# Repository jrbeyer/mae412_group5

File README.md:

# Custom Model Train System With Pan-Tilt Tracking, Positioning, and Aiming Sentries

This repository contains the codebase for a custom model train system control. The system uses two pan-tilt turrets, one for searching and tracking a train as it follows a track, and the other for hitting the train with a laser from any region of the track.

## System Overview

The system is designed around two custom 3D printed pan-tilt turrets, each equipped with a NEMA 17 stepper motor, variable current motor drivers, and AS5600 motor encoders. The turrets use specific ratio gear pulleys for precise control.

The train system is controlled by a Hornbee train controller system and a custom microprocessor implemented on a scotchflex vector board consisting of an EEPROM, ACIA, and other components. The system interfaces with two ESP32-S2-Minis and custom power sensor fusion and motor control boards.

## Features

- **Train Tracking**: Uses a PixyCam and a Time-of-Flight (ToF) sensor to search and track the train. The system outputs the global coordinates of the train via ESP32.
- **Laser Control**: Takes in the reported coordinates of the train and controls a laser to hit the train from any region of the track.

## Hardware Requirements

- ESP32-S2-Minis
- PixyCam
- Time-of-Flight (ToF) sensor
- Pan-Tilt Turrets (Custom 3D printed)
- NEMA 17 Stepper Motors
- Variable Current Motor Drivers
- AS5600 Motor Encoders
- Specific Ratio Gear Pulleys
- Laser Pointer
- Hornbee Train Controller System
- Custom Microprocessor (Implemented on a Scotchflex Vector Board)
- Custom Power Sensor Fusion and Motor Control Boards

## Software Requirements

- Arduino IDE
- VL53L0X Library
- Pixy Library
- BasicStepperDriver Library

## Setup

1. Connect the PixyCam and ToF sensor to the ESP32.
2. Connect the pan-tilt turrets to the ESP32.
3. Connect the laser pointer to the ESP32.
4. Open the `mae412_group5.ino` file in the Arduino IDE.
5. Upload the code to the ESP32.

## Usage

The system operates in three states:

- **Inactive**: The system is idle and the steppers are disabled.
- **Search**: The system searches for the train using the PixyCam and ToF sensor. The steppers are enabled and move the turret to track the train.
- **Lock**: The system locks onto the train and the laser pointer is activated. The turret moves to follow the train and the laser pointer adjusts to hit the train.

## Contributing

Pull requests are welcome. For major changes, please open an issue first to discuss what you would like to change.

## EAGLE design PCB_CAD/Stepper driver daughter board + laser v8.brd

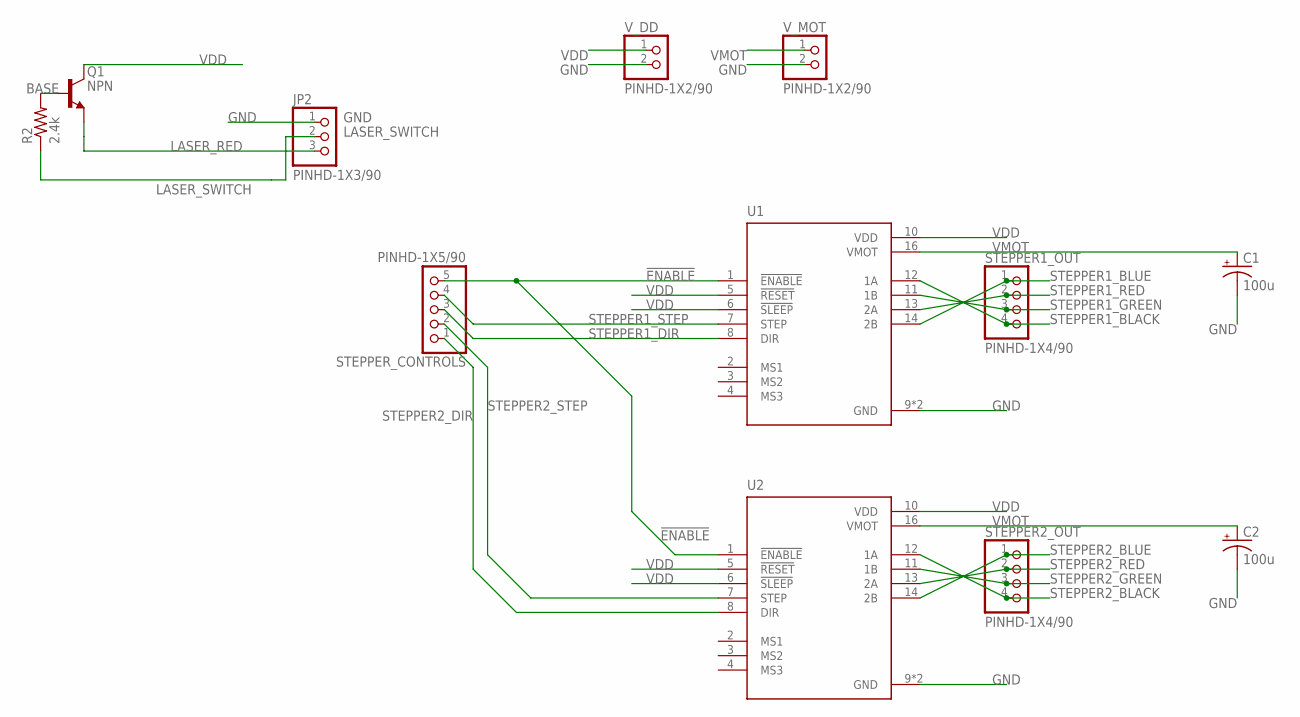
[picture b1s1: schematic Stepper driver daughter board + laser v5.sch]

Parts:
C1, C2: 100u; E22-6
JP2: PINHD-1X3/90; 1X03/90
Q1: NPN; TO92
R2: 2.4k; 0207/10
STEPPER1_OUT, STEPPER2_OUT: PINHD-1X4/90; 1X04/90
STEPPER_CONTROLS: PINHD-1X5/90; 1X05/90
U1, U2: A4988_STEPPER_MOTOR_DRIVER_CARRIER; MODULE_A4988_STEPPER_MOTOR_DRIVER_CARRIER
V_DD: PINHD-1X2/90; 1X02/90
V_MOT: PINHD-1X2/90; 1X02/90

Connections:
!ENABLE: STEPPER_CONTROLS.5, U1.1 (!ENABLE), U2.1 (!ENABLE)
BASE: Q1.2 (B), R2.2
GND: C1.-, C2.-, JP2.1, U1.9 (GND), U1.15 (GND), U2.9 (GND), U2.15 (GND), V_DD.2, V_MOT.2
LASER_RED: JP2.3, Q1.1 (E)
LASER_SWITCH: JP2.2, R2.1
STEPPER1_BLACK: STEPPER1_OUT.4, U1.12 (1A)
STEPPER1_BLUE: STEPPER1_OUT.1, U1.14 (2B)
STEPPER1_DIR: STEPPER_CONTROLS.3, U1.8 (DIR)
STEPPER1_GREEN: STEPPER1_OUT.3, U1.11 (1B)
STEPPER1_RED: STEPPER1_OUT.2, U1.13 (2A)
STEPPER1_STEP: STEPPER_CONTROLS.4, U1.7 (STEP)
STEPPER2_BLACK: STEPPER2_OUT.4, U2.12 (1A)
STEPPER2_BLUE: STEPPER2_OUT.1, U2.14 (2B)
STEPPER2_DIR: STEPPER_CONTROLS.1, U2.8 (DIR)
STEPPER2_GREEN: STEPPER2_OUT.3, U2.11 (1B)
STEPPER2_RED: STEPPER2_OUT.2, U2.13 (2A)
STEPPER2_STEP: STEPPER_CONTROLS.2, U2.7 (STEP)
VDD: Q1.3 (C), U1.5 (!RESET), U1.6 (!SLEEP), U1.10 (VDD), U2.5 (!RESET), U2.6 (!SLEEP), U2.10 (VDD), V_DD.1
VMOT: C1.+, C2.+, U1.16 (VMOT), U2.16 (VMOT), V_MOT.1

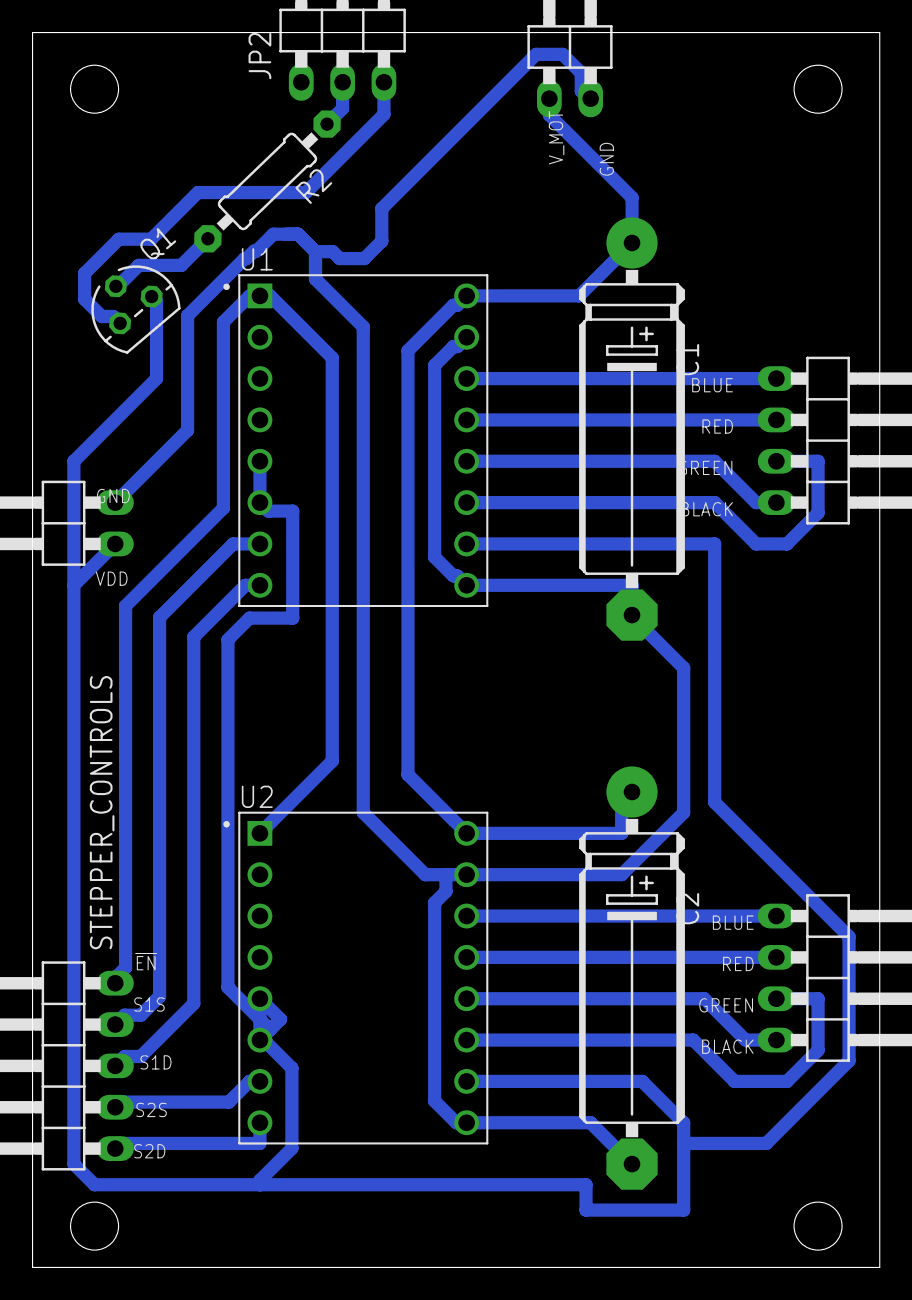
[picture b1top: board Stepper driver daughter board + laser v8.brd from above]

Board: 2 copper layers, 52.0 x 75.9 mm, 12 parts (0 on the bottom side), 19 nets.

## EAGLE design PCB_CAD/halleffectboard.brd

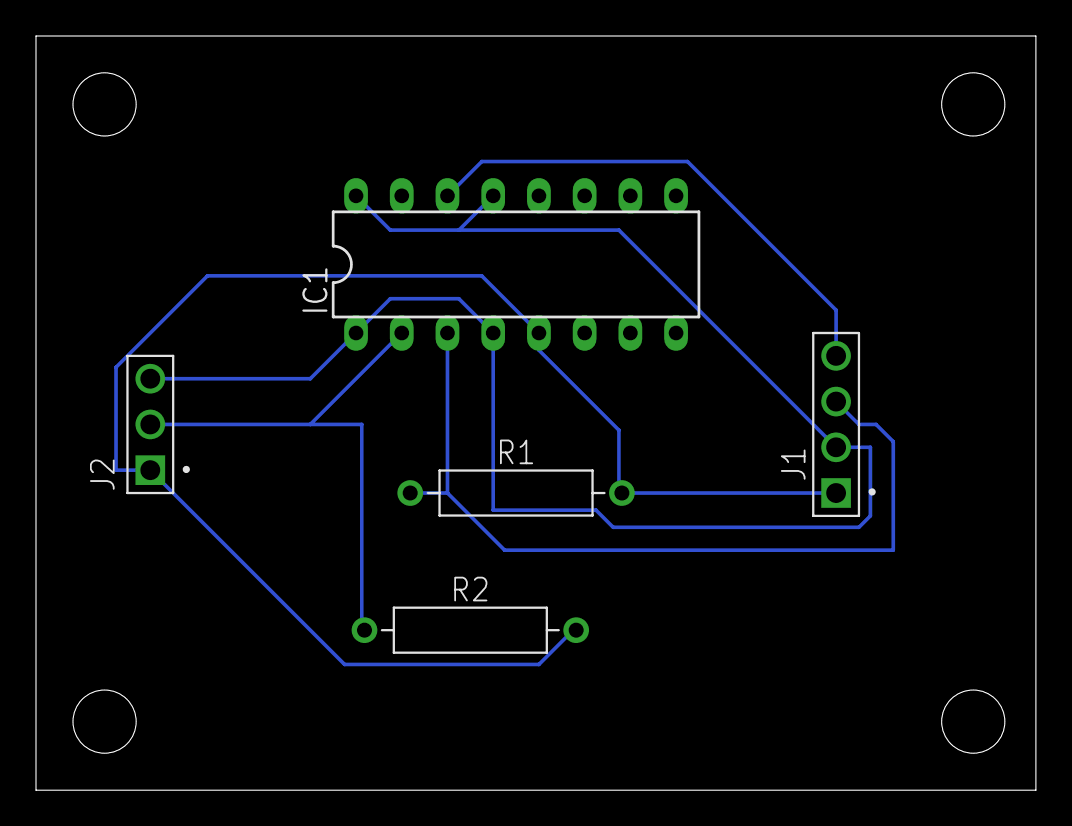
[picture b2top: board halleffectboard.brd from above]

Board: 2 copper layers, 55.5 x 41.9 mm, 5 parts (0 on the bottom side), 5 nets.

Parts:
IC1: 7476N; DIL16
J1: 61300411121
J2: 61300311121
R1, R2: RESAD1176W63L850D250B

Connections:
CLR: IC1.3, J1.3, R1.1
GND: IC1.1, IC1.4, IC1.13, IC1.16, J1.2, J2.3
HALL: IC1.2, J2.2, R2.1
OUT: IC1.14, J1.4
VCC: IC1.5, J1.1, J2.1, R1.2, R2.2

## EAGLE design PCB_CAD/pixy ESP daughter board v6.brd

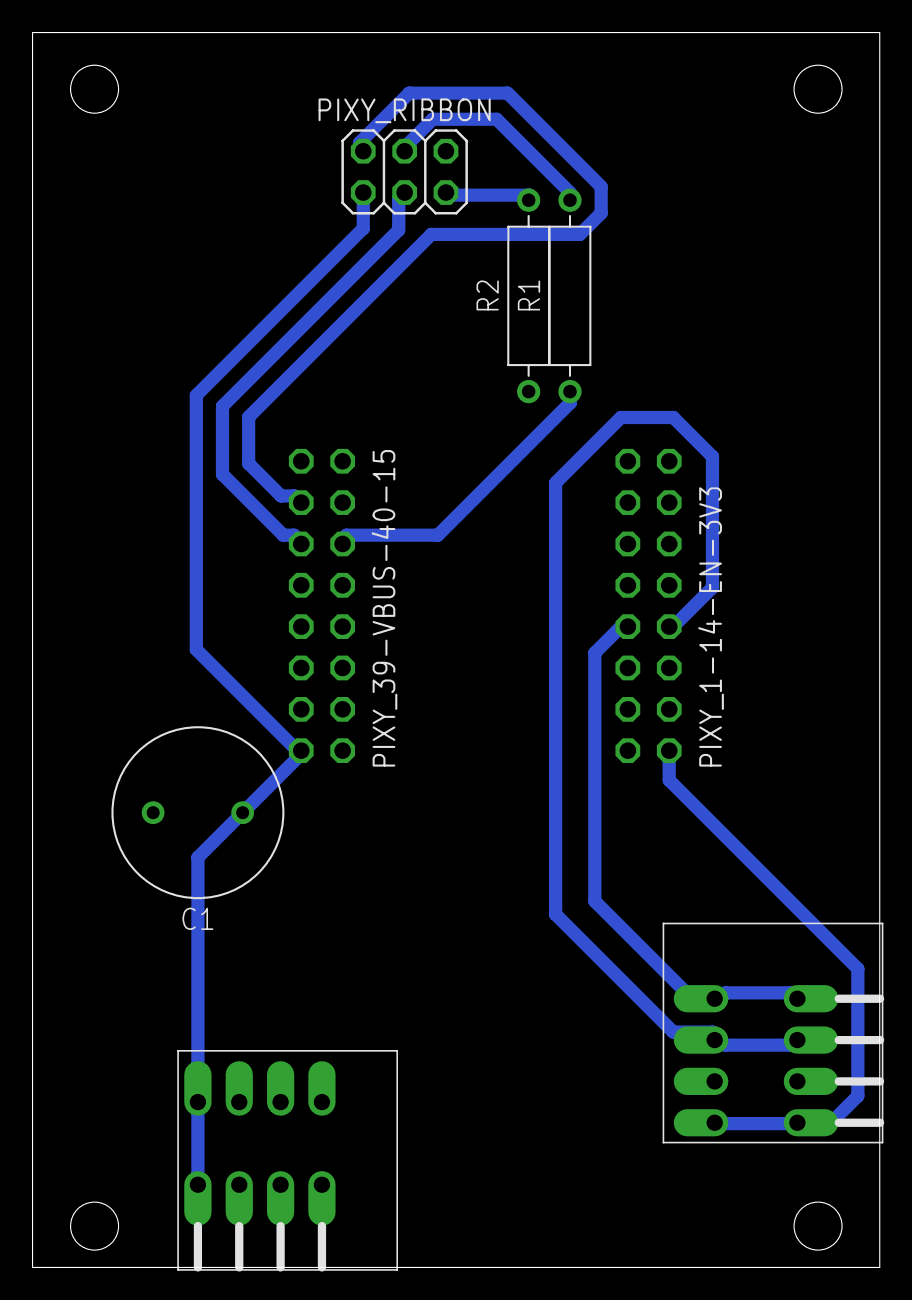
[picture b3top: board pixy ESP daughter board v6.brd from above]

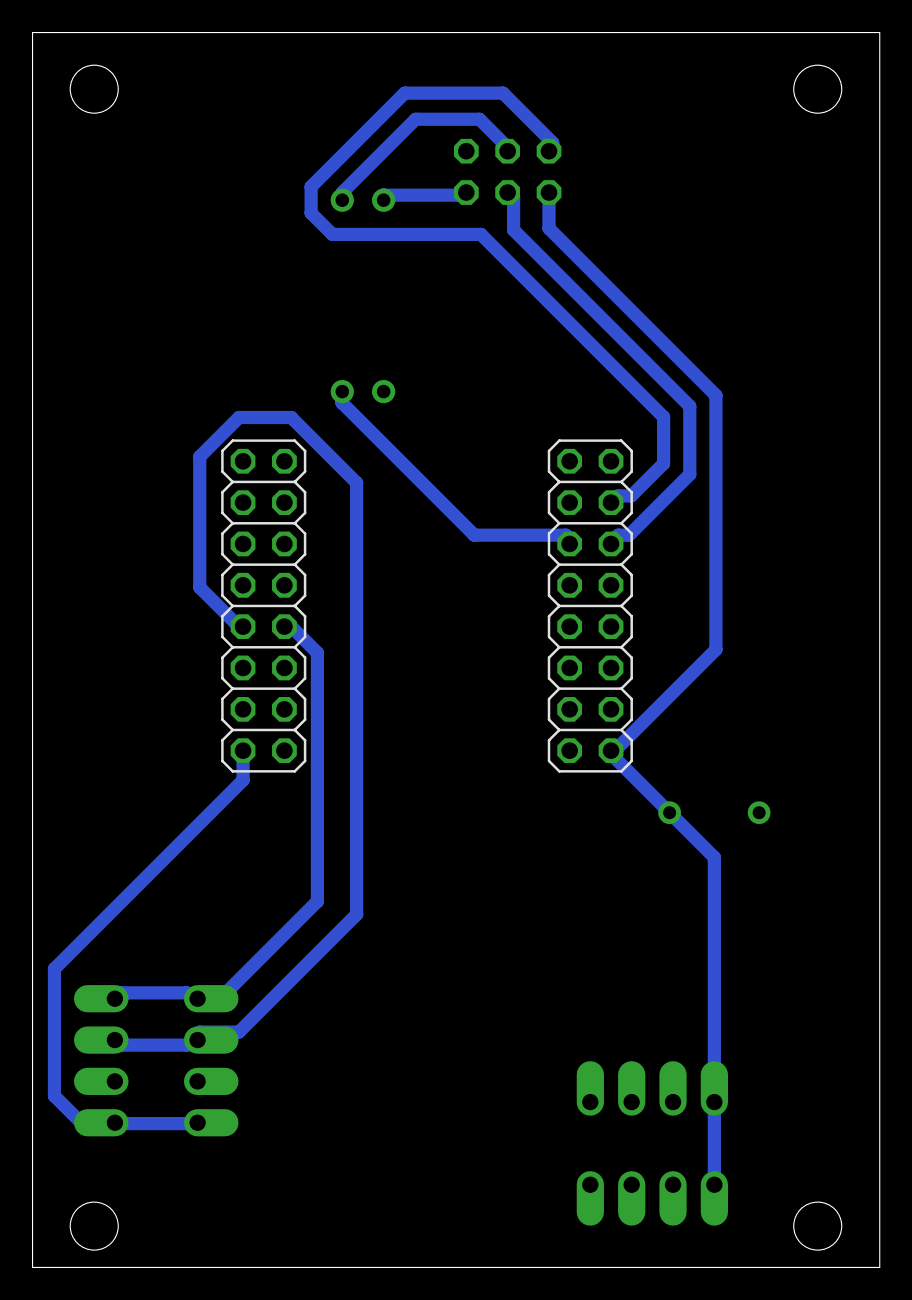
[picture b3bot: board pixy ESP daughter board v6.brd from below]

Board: 2 copper layers, 52.0 x 75.9 mm, 8 parts (2 on the bottom side), 10 nets.

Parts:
C1: 10u; CAPRD550W60D1025H1250B
PIXY_1-14-EN-3V3, PIXY_39-VBUS-40-15: PINHD-2X8; 2X08
PIXY_RIBBON: PINHD-2X3; 2X03
POWER_IN: TE_CONN_1-2834016-4; 1-2834016-4
R1, R2: 0; RESAD1176W63L850D250B
VL53L0X1: TE_CONN_1-2834016-4; 1-2834016-4

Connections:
3V3: PIXY_1-14-EN-3V3.2, VL53L0X1.P$1, VL53L0X1.P$2
35: PIXY_39-VBUS-40-15.11, PIXY_RIBBON.3
36: PIXY_39-VBUS-40-15.12, R1.1
36_PIXY: PIXY_RIBBON.4, R1.2
37: PIXY_39-VBUS-40-15.13, PIXY_RIBBON.2
GND: C1.2, PIXY_39-VBUS-40-15.3, PIXY_39-VBUS-40-15.4, POWER_IN.P$3, POWER_IN.P$4, POWER_IN.P$5, POWER_IN.P$6, POWER_IN.P$7, POWER_IN.P$8, R2.1, VL53L0X1.P$3, VL53L0X1.P$4
GND_PIXY: PIXY_RIBBON.5, R2.2
SCL: PIXY_1-14-EN-3V3.8, VL53L0X1.P$5, VL53L0X1.P$6
SDA: PIXY_1-14-EN-3V3.7, VL53L0X1.P$7, VL53L0X1.P$8
VDD: C1.1, PIXY_39-VBUS-40-15.1, PIXY_RIBBON.1, POWER_IN.P$1, POWER_IN.P$2

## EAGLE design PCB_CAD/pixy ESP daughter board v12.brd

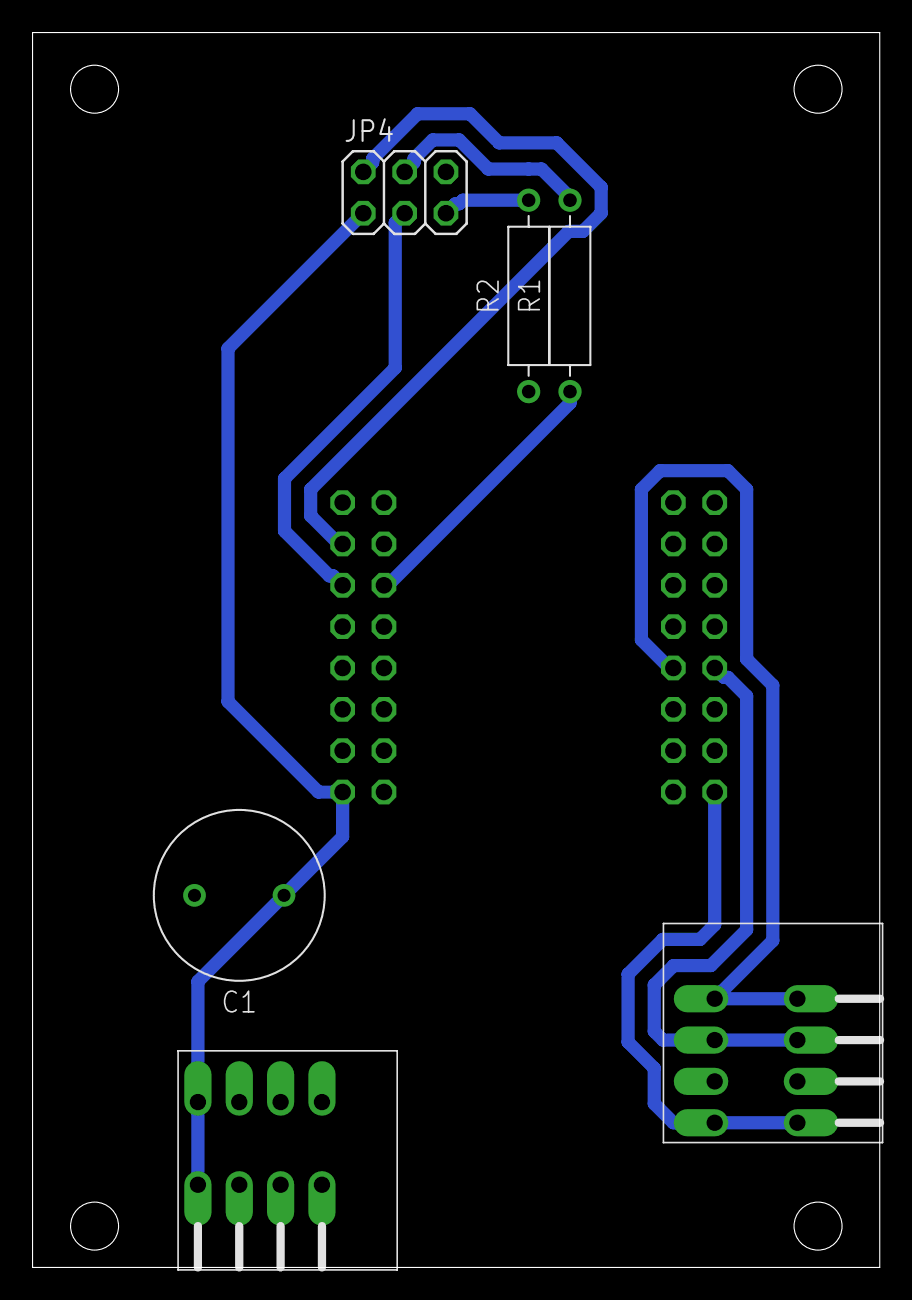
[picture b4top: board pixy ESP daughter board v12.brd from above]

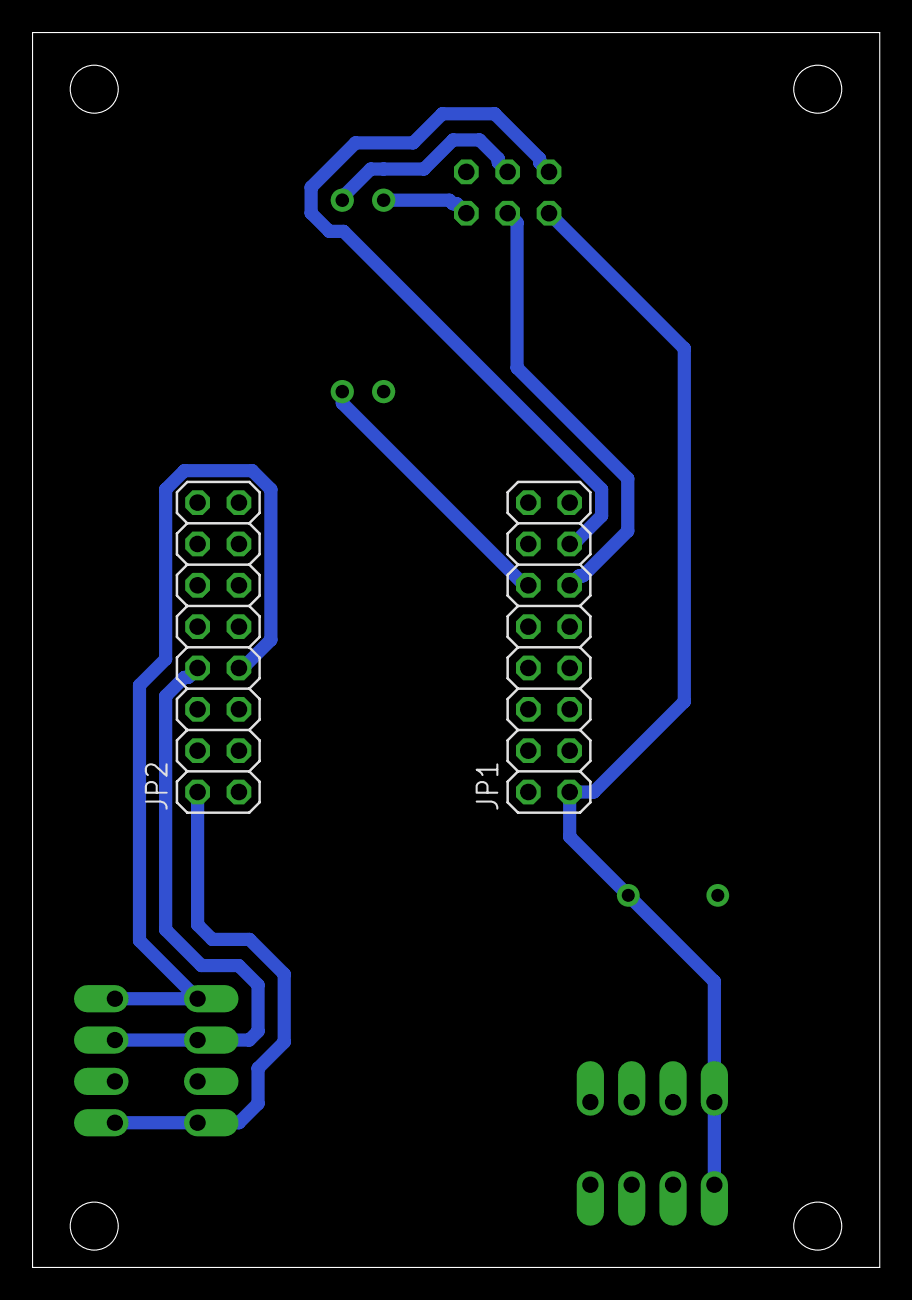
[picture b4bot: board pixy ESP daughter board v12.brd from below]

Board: 2 copper layers, 52.0 x 75.9 mm, 8 parts (2 on the bottom side), 10 nets.

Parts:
C1: 10u; CAPRD550W60D1025H1250B
JP1, JP2: PINHD-2X8; 2X08
JP4: PINHD-2X3; 2X03
POWER_IN: TE_CONN_1-2834016-4; 1-2834016-4
R1, R2: 0; RESAD1176W63L850D250B
VL53L0X1: TE_CONN_1-2834016-4; 1-2834016-4

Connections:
3V3: JP2.2, VL53L0X1.P$1, VL53L0X1.P$2
35: JP1.11, JP4.3
36: JP1.12, R1.1
36_PIXY: JP4.4, R1.2
37: JP1.13, JP4.2
GND: C1.2, JP1.3, JP1.4, POWER_IN.P$3, POWER_IN.P$4, POWER_IN.P$5, POWER_IN.P$6, POWER_IN.P$7, POWER_IN.P$8, R2.1, VL53L0X1.P$3, VL53L0X1.P$4
GND_PIXY: JP4.5, R2.2
SCL: JP2.8, VL53L0X1.P$5, VL53L0X1.P$6
SDA: JP2.7, VL53L0X1.P$7, VL53L0X1.P$8
VDD: C1.1, JP1.1, JP4.1, POWER_IN.P$1, POWER_IN.P$2

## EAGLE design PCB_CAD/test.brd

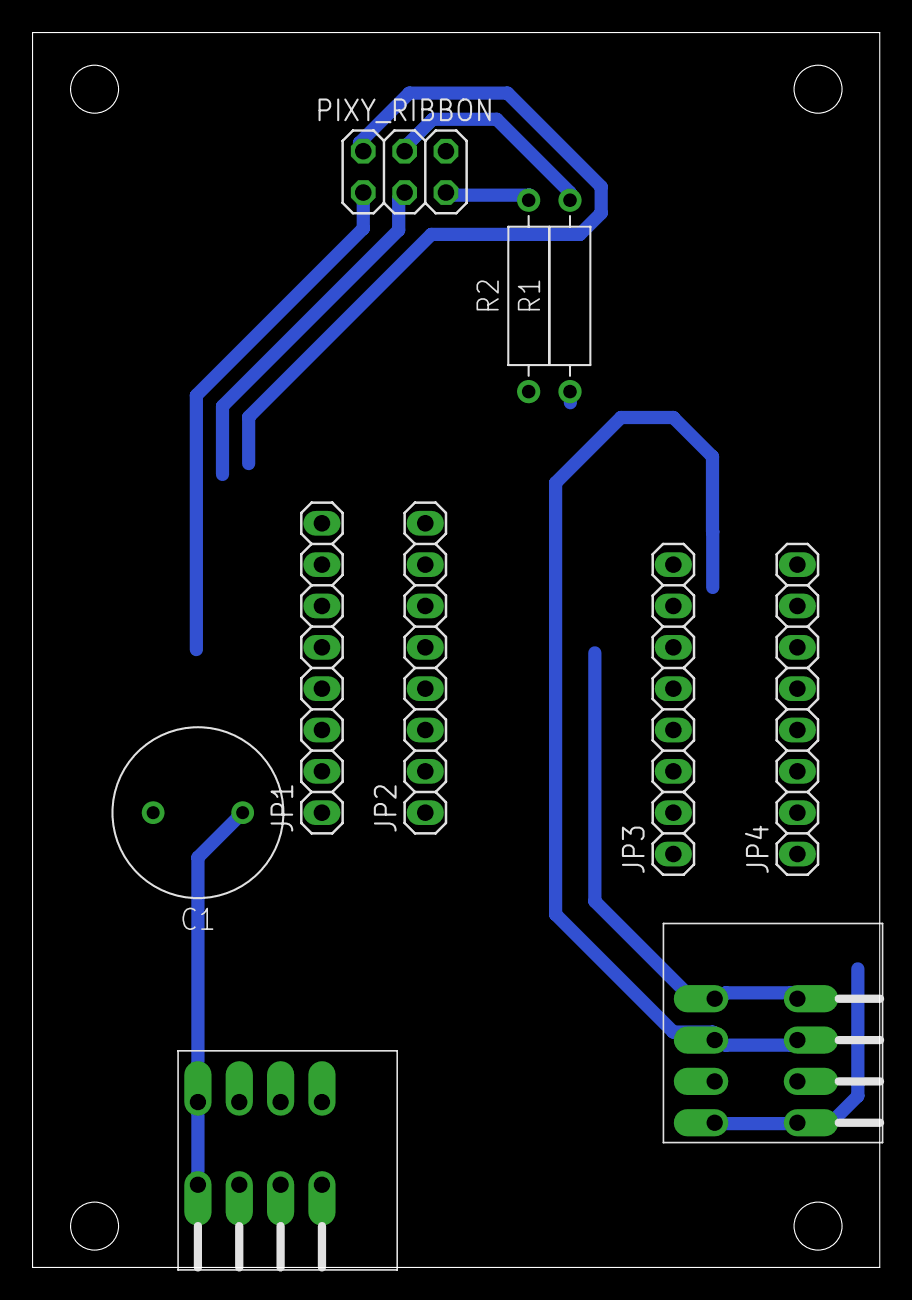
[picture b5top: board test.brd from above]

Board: 2 copper layers, 52.0 x 75.9 mm, 10 parts (0 on the bottom side), 10 nets.

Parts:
C1: 10u; CAPRD550W60D1025H1250B
JP1, JP2, JP3, JP4: PINHD-1X8; 1X08
PIXY_RIBBON: PINHD-2X3; 2X03
POWER_IN: TE_CONN_1-2834016-4; 1-2834016-4
R1, R2: 0; RESAD1176W63L850D250B
VL53L0X1: TE_CONN_1-2834016-4; 1-2834016-4

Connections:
3V3: JP4.1, VL53L0X1.P$1, VL53L0X1.P$2
35: JP1.6, PIXY_RIBBON.3
36: JP2.6, R1.1
36_PIXY: PIXY_RIBBON.4, R1.2
37: JP1.7, PIXY_RIBBON.2
GND: C1.2, JP1.2, JP2.2, POWER_IN.P$3, POWER_IN.P$4, POWER_IN.P$5, POWER_IN.P$6, POWER_IN.P$7, POWER_IN.P$8, R2.1, VL53L0X1.P$3, VL53L0X1.P$4
GND_PIXY: PIXY_RIBBON.5, R2.2
SCL: JP4.4, VL53L0X1.P$5, VL53L0X1.P$6
SDA: JP3.4, VL53L0X1.P$7, VL53L0X1.P$8
VDD: C1.1, JP1.1, PIXY_RIBBON.1, POWER_IN.P$1, POWER_IN.P$2

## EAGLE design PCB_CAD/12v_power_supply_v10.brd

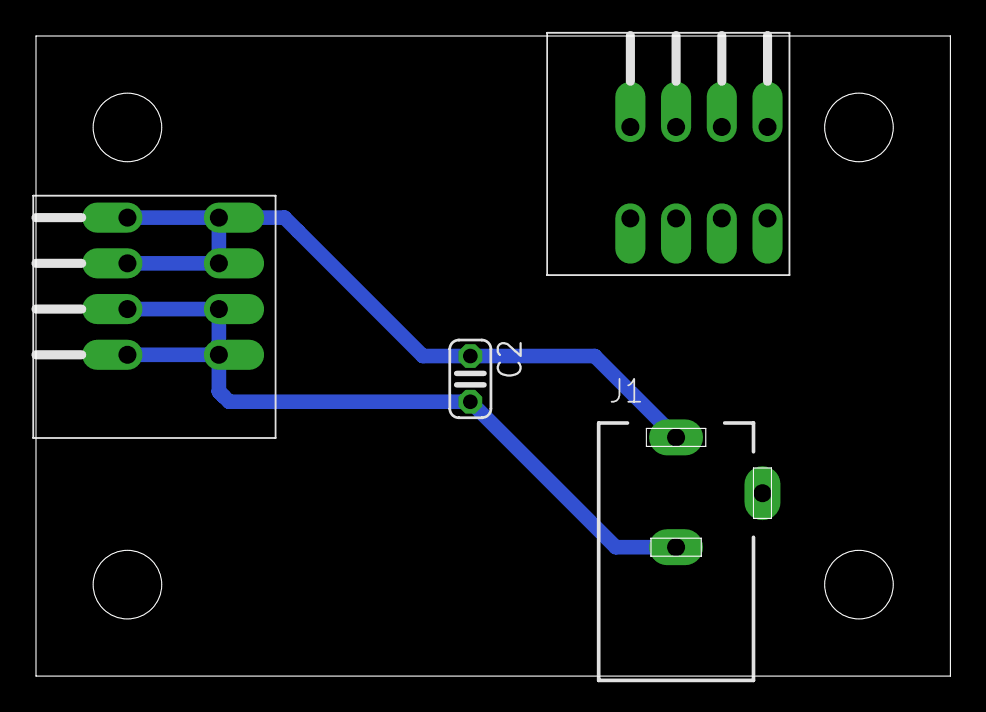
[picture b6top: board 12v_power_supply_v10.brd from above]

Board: 2 copper layers, 50.8 x 35.6 mm, 4 parts (0 on the bottom side), 2 nets.

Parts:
C2: ~0.33u; C025-024X044
J1: DCJ0202
U$1, U$2: TE_CONN_1-2834016-4; 1-2834016-4

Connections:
+V: C2.1, J1.1, U$1.P$1, U$1.P$2, U$1.P$3, U$1.P$4
GND: C2.2, J1.3, U$1.P$5, U$1.P$6, U$1.P$7, U$1.P$8, U$2.P$1, U$2.P$2, U$2.P$3, U$2.P$4, U$2.P$5, U$2.P$6, U$2.P$7, U$2.P$8

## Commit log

2024-04-06 start I2C comms, ADC config, Pixy config
    Untested!
2024-04-06 Start rangefinder conversion procedure
2024-04-07 Add some unit tests
2024-04-07 add pinout information, fix a unit test
2024-04-09 Tested pixycam, watchdog timer for getBlocks()
2024-04-15 New distance sensor integrated, but pixy probs
2024-04-15 fix pixycam issues
2024-04-16 add example laser pointer code
2024-04-20 New defines for stepper motors
2024-04-20 Add stepper driver initialization
2024-04-20 rename for consistency
2024-04-20 Initialize PID params (dummy values)
2024-04-21 (untested) PID skeleton, code cleanup
2024-04-23 PID execution unit testing
2024-04-25 start tuning PID
2024-04-29 GOOD PID PARAMETERS HERE!!!!!!
2024-05-03 convert timer infrastructure to ESP32
2024-05-03 testing for open-loop positioning of servos
2024-05-03 preparing for wifi overhaul
2024-05-03 WIRELESS TRACKING
2024-05-03 Separate unit tests, remove deprecated code
2024-05-03 compile issue
2024-05-04 I2C ESP<->Mini (soon to be vector board arduino)
2024-05-04 configure vector board arduino for ACIA serial
2024-05-04 Add encoder count estimate
2024-05-04 Enforcing position clips
2024-05-04 tracking is reasonably robust
2024-05-04 Homing functionality
    Updating pin definitions in VB arduino
2024-05-04 remove test code
2024-05-04 update todos
2024-05-04 gate PID execution on control_state
2024-05-05 Defines for hall effect and switching
2024-05-05 Smart enable/disable of steppers
2024-05-05 Integrate kill switch
2024-05-05 implement switch-throwing state machine
2024-05-05 Add thresholding+hysteresis to hall effect
2024-05-05 ignore these changes
2024-05-05 swapped turnout signals
2024-05-05 badswitching code
2024-05-05 Search_v1
2024-05-05 finalize search code changes
2024-05-06 README.md first draft
2024-05-07 initialize and disable motors right away
2024-05-08 startup routine
2024-05-08 i2c working between vector board arduino
2024-05-08 progress toward ACIA communication
2024-05-08 untested VIA connection
2024-05-08 first draft incorporating laser pointer
2024-05-08 New motor enable pinout
2024-05-08 bababooey
2024-05-09 EAGLE, Fusion, AnyRail, Vector, GAL
    CAD and code files for project
2024-05-11 Targeting nominally working
2024-05-11 refactor communications
2024-05-11 targeting sometimes works
2024-05-13 rebounded and changed when laser movement happens
2024-05-14 turn laser off first thing!
2024-05-15 new offset values
2024-05-15 clean up code
2024-05-15 240->80 Hz
2024-05-15 update arduino comms request
2024-05-15 fix VIA handling bug

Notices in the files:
parts and their libraries:
1-2834016-4: Licensing: Creative Commons ShareAlike 4.0 International - https://creativecommons.org/licenses/by-sa/4.0
